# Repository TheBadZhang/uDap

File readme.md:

# uDap

uDap 是一个低成本低占面积低外围设计的单芯片 USB 设备同时提供 SWD 调试和一路虚拟串口，或者其他功能。功能可以通过上位机切换或者开启，可以实现多个功能同时工作，大幅度提升开发调试效率

> 设计要求：整个调试器物料成本小于10元，芯片主控引脚数量小于等于48，且要足够大众，产品生命周期长

核心优势如下：
1. 支持 **SWD** 调试协议，用更低的成本实现更高的性能，适配 Cortex-M 系列，STM32、GD32、AT32、CW32、PY32、HK32 等。
2. 集成 **USB2UART** 功能，支持多种波特率，满足大量数据传输和日志打印的需求
3. **UF2 bootloader**：上电长按 PB3 出现一个 U 盘，把 `firmware.uf2` 拖进去就能升级，
   不需要再接线烧录；也可以由上位机发 vendor command 直接进 bootloader
4. **功能可由上位机配置**（vendor command）：单串口+流控 / 双串口、两颗 LED 的功能、
   调试器模式切换、读芯片 UID，设置掉电保存
5. 提供 **5V/3.3V** 双路电源输出

```mermaid
flowchart LR
    PC["主机<br/>Jlink / OpenOCD / pyOCD / 串口终端"]
    subgraph DAP["uDap2 (CH32X035F8U)"]
        USBFS["USB 全速设备"]
        DAPC["CMSIS-DAP<br/>DAP.c + sw_dp.c"]
        BR["CDC 串口桥<br/>drv_uart.c"]
    end
    TGT["目标板<br/>SWCLK / SWDIO / nRESET"]
    UART["目标板 USART<br/>PB0=TX / PB1=RX"]

    PC -- "USB bulk (CMSIS-DAP)" --> USBFS
    PC -- "USB CDC ACM" --> USBFS
    USBFS --> DAPC
    USBFS --> BR
    DAPC -- "SWD 位翻转" --> TGT
    BR -- "USART" --> UART
```

### uDap-CH32X035F8U6

- 调试器 ①：**CMSIS-DAP**（bulk，WinUSB）——OpenOCD / pyOCD / probe-rs 可直接使用。**固定编入**
- 调试器 ②：**WCH-Link**（RVSWD，`1a86:8010`）——支持 CH32X03X / CH32L10X / CH32V20X /
  CH32V30X / CH58X / CH59X 六个目标族。**可选编译**（`build.ps1 -Wchlink y`，默认不编），
  编入后上电时**按住 PB3**切到另一种调试器模式
- 桥接串口 ①：CDC ACM ↔ 目标板 USART4（PB0=TX / PB1=RX），**不限制波特率**
- 桥接串口 ②（双串口模式）：CDC ACM ↔ USART2（PA2=TX2 / PA3=RX2），独立波特率
- PA2 / PA3 **双用途**：`DTR` + `RTS`（低有效）或 `TX2`/`RX2`，按键**双击**切换、掉电保存
- **串口模式决定 USB 里有几个 CDC**：单串口 + 流控只枚举 1 个 COM 口（USART2 关闭），
  双串口枚举 2 个；切换模式会重新枚举一次
- **COM1 的接收走 DMA**（USART4_RX = DMA1_Channel8，1 KB 环形缓冲）：逐字节 RXNE
  中断从每秒 10 万次降到「每半个缓冲一次」，高波特率下不再因 ISR 延迟触发 ORE
  丢字节。TX（含 COM2 全部方向）仍用中断 —— 实测给 TX 挂 DMA（Ch1 / Ch7）会让
  对应串口卡死，原因未定位。注意 USB IN 侧的总吞吐天花板（≈190~200 KiB/s）与
  DMA 无关，双口同时满速时仍受它限制
- SWD 时钟：请求 **≥6 MHz** 自动切「快路径」，**6 MHz 与更高同速**，推荐就填 6 MHz
- SWD 吞吐（STM32F411 目标，64 KiB 块）：**pyocd 262 写 / 232 读 KiB/s**、
  OpenOCD 149 / 148、probe-rs 155 / 140 —— 见「性能实测」一节
- **只留 SWD 的构建**（`--uart=n`）：USB 里没有 CDC，主机不再轮询串口端点、
  主循环也不再跑 CDC 桥接 —— 实测写 **278 KiB/s**（RAM 写，比带串口构建约 +6%）
- 串口环回：**2 Mbaud 持续满载零丢字节**（96~98 % 利用率）；分块发送时 6 Mbaud 亦字节无误
- 桥接吞吐天花板：约 **190~200 KiB/s**（≈2 Mbaud），受 USB IN 侧调度限制，与 USB 带宽无关

| 信号 | 引脚 | 说明 |
| --- | --- | --- |
| SWCLK | PA5 | SWD 时钟 |
| SWDIO | PA6 | SWD 双向数据（CFGLR 动态切输入/输出） |
| nRESET | PA7 | RST 复位 |
| DTR / TX2 | PA2 | 流控模式 = DTR（低有效）；双串口模式 = 串口2 TX |
| RTS / RX2 | PA3 | 流控模式 = RTS（低有效）；双串口模式 = 串口2 RX |
| TX | PB0 | 串口1 TX |
| RX | PB1 | 串口1 RX |
| 模式按键 | PB3 | 上拉输入，按下接地；上电一直按住 >1.2 s 进 UF2，运行中双击切模式（单模式=串口/双模式=调试器） |
| DAP 灯 | PB11 | 低电平点亮；默认 = CMSIS-DAP 连接时亮（也可由 vendor command 切换用途） |
| UART 灯 | PB12 | 低电平点亮；默认 = 亮表示双串口模式（也可由 vendor command 切换用途） |
| USB | PC16 = DPDM / PC17 = DP | 固定复用 |

### uDap-CH32X033

与 uDap-CH32X035F8U6 **同一份固件**（CH32X033 的 SDK/外设与 X035 相同，差别只有引脚
与 USB PD/CC 外设），换一张板级表就行：

```powershell
.\build.ps1 -Board ch32x033
```

| 信号 | 引脚 | 说明 |
| --- | --- | --- |
| SWCLK / SWDIO | PA1 / PA0 | CMSIS-DAP + WCH-Link（互斥），默认方案 `pa0_pa1` |
| nRESET | PA9 | 目标复位，低有效（开漏模拟） |
| RX1 / TX1 | PA3 / PA2 | 串口1，USART2 默认引脚 |
| TX2 / RX2 | PA10 / PA11 | 串口2，USART1 + `USART1_RM = 01` |
| 模式按键 | PC3 | 上拉输入，按下接地；长按进 UF2，双击切模式 |
| LED（DAP / UART） | PB7 / PB1 | 低电平点亮 |
| USB | PC16 = DPDM / PC17 = DP | 固定复用 |
| DTR / RTS | 无 | 本板没有这两个脚，默认串口模式为双串口 |

### uDap-CH32V203F8U6

### uDap-CH572

### uDap-CH552G

## 对照测试

本节把「本板 uDAP 以外的第三方 CMSIS-DAP 探针」的 SWD 吞吐测试集中在一处：
测试方法、五块探针的标识、以及**唯一的总表**（按频率 × 块大小 × 调试器排成矩阵）。
各探针不再单独列表，避免与总表重复。

#### 测试对象与接线

| 项目 | 值 |
| --- | --- |
| 目标 | STM32F411CEU6（CPUID `0x410FC241`、DBGMCU IDCODE `0x10006431` → DEV_ID `0x431`、512 KB Flash、128 KB SRAM） |
| 测试区 | 目标 SRAM `0x20000000` 起（与 18.1、18.5 同一地址，便于对比） |
| 接线 | 探针 SWCLK / SWDIO / GND 接目标，目标单独供电 |

#### 测量流程

1. 打开探针会话、`halt` 目标；
2. **整块备份**测试区，测完**逐字写回**并 `resume`，不破坏目标正在跑的程序；
3. 填充模式 `0xA5A50000 | i`（变化的 pattern，能暴露地址线/数据线问题与突发顺序错误）；
4. 每个「频率 × 块大小」组合先预热一次，再正式测 5 次；写、读**各自单独计时**，
   读回**逐字校验**；失败（ACK 错 / 超时 / 数据不符）记 `ok=0` 并继续；
5. 每组取**中位数**（不取平均，避免个别离群值污染）。

> 本板 uDAP 的 OpenOCD 数据于 2026-10-28 使用 `firmware/tools/speed.ps1 -Rounds 1` 逐组合复测；每组预热 2 轮后正式测 1 轮，因此该探针的数据为单次结果，不适用上述 5 次中位数流程。

#### 参数与工具

| 参数 | 取值 |
| --- | --- |
| 频率 | **1 / 3 / 6 / 9 / 12 / 15 MHz**（6 档；表头「1、3、6…」即 MHz） |
| 块大小 | **1 / 4 / 16 / 64 KiB**（4 档） |
| 重复次数 | 每组合 **5 次**，取中位数 |
| 工具 | **pyocd 0.45.1** 与 **OpenOCD 0.12.0**，同一块探针各扫一遍 |

两个工具都支持在**同一条会话里改频率**（pyocd 用 `probe.set_clock()`，OpenOCD 用
`adapter speed`），所以整轮扫描只连接一次，不会把反复连接的固定开销算进结果。

> 表里的频率是**请求值**，不是实测 SWCLK。探针可能把请求值映射成离散分频，
> 实际时钟与请求值有差距（见下面「注意事项」里的低端反常）。

#### 五块探针的标识

| 探针 | 主机侧名称 | 序列号 | CMSIS-DAP | 备注 |
| --- | --- | --- | --- | --- |
| **本板 uDAP** | `uDAP CMSIS-DAP` | `923CABCDFB83BD7AFFFFFFFF` | 0.1.0 | 本仓库固件；快路径时钟约 6 MHz；无 WebUSB/MSC |
| **FanX Tek DAPLink** | `Arm DAPLink CMSIS-DAP` | `38b30f94aae9ddfa01` | FW 2.1.0，v2(bulk) | SWD+JTAG+SWO-UART；`Packet Count = 4` |
| **CherryUSB CH32V305** | `CherryUSB CMSIS-DAP` | `39D9ABCD` | FW 2.1.1，v2 | 自制板；**pyocd 不可用**（见下） |
| **LuatOS Air32 MINI** | `ABrobot CMSIS-DAP` | `000100011a5a5bb6000000000003f60fa5a5a5a597969908` | FW 2.1.0，v1(HID)+v2 | `Packet Count = 100`；**读快于写**；**吞吐会跳档**（见下） |
| **SLogic 8** | `SIPEED RV CMSIS-DAP` | `012345ABCDEF` | FW 2.1.0，v2 | Sipeed 板，VID:PID 为 `d6e7:3507`（**与其余四块不同**）；`Packet Count = 8` |

> 前四块的 VID:PID 都是 `0d28:0204`，同时插入时**必须**用序列号区分：
> OpenOCD 侧 `-c "adapter serial <id>"`，pyocd 侧 `unique_id`。序列号用 `pyocd list` 查。

#### 总表：OpenOCD（写 / 读，KiB/s；本板 uDAP 为单次结果，其余为 5 次中位数）

| 调试器 | 块大小 | 1 | 3 | 6 | 9 | 12 | 15 |
| --- | --- | ---: | ---: | ---: | ---: | ---: | ---: |
| 本板 uDAP (CH32X035) | 1 KiB | 26 / 24 | 60 / 61 | 259 / 219 | 234 / 232 | 247 / 233 | 255 / 218 |
| 本板 uDAP (CH32X035) | 4 KiB | 27 / 25 | 60 / 64 | 268 / 248 | 269 / 249 | 267 / 246 | 269 / 248 |
| 本板 uDAP (CH32X035) | 16 KiB | 27 / 25 | 61 / 64 | 267 / 249 | 267 / 249 | 268 / 249 | 267 / 250 |
| 本板 uDAP (CH32X035) | 64 KiB | 27 / 25 | 61 / 64 | 266 / 251 | 266 / 250 | 267 / 251 | 267 / 251 |
| FanX Tek DAPLink | 1 KiB | 177 / 179 | 250 / 237 | 278 / 279 | 314 / 307 | 500 / 333 | 500 / 366 |
| FanX Tek DAPLink | 4 KiB | 185 / 197 | 258 / 269 | 318 / 323 | 302 / 313 | 462 / 437 | 456 / 444 |
| FanX Tek DAPLink | 16 KiB | 185 / 193 | 258 / 262 | 315 / 325 | 303 / 304 | 461 / 458 | 464 / 470 |
| FanX Tek DAPLink | 64 KiB | 182 / 183 | 258 / 263 | 307 / 307 | 302 / 303 | 457 / 469 | 458 / 468 |
| CherryUSB CH32V305 | 1 KiB | 107 / 125 | 200 / 200 | 242 / 250 | 333 / 333 | 390 / 390 | 475 / 378 |
| CherryUSB CH32V305 | 4 KiB | 116 / 119 | 195 / 205 | 254 / 269 | 412 / 399 | 426 / 400 | 425 / 400 |
| CherryUSB CH32V305 | 16 KiB | 117 / 120 | 197 / 206 | 261 / 275 | 427 / 398 | 428 / 405 | 450 / 410 |
| CherryUSB CH32V305 | 64 KiB | 117 / 121 | 198 / 206 | 261 / 275 | 426 / 396 | 425 / 400 | 439 / 416 |
| LuatOS Air32 MINI | 1 KiB | 130 / 125 | 200 / 200 | 248 / 250 | 277 / 250 | 250 / 234 | 250 / 250 |
| LuatOS Air32 MINI | 4 KiB | 128 / 128 | 216 / 208 | 241 / 235 | 267 / 267 | 261 / 268 | 267 / 267 |
| LuatOS Air32 MINI | 16 KiB | 130 / 128 | 213 / 207 | 251 / 246 | 276 / 275 | 268 / 265 | 274 / 267 |
| LuatOS Air32 MINI | 64 KiB | 129 / 130 | 215 / 210 | 252 / 245 | 276 / 274 | 268 / 265 | 272 / 269 |
| SLogic 8 (Sipeed) | 1 KiB | 59 / 58 | 105 / 105 | 130 / 129 | 147 / 143 | 169 / 155 | 148 / 151 |
| SLogic 8 (Sipeed) | 4 KiB | 60 / 60 | 108 / 108 | 132 / 131 | 157 / 147 | 166 / 159 | 166 / 160 |
| SLogic 8 (Sipeed) | 16 KiB | 59 / 59 | 110 / 109 | 135 / 131 | 155 / 148 | 166 / 158 | 166 / 159 |
| SLogic 8 (Sipeed) | 64 KiB | 59 / 59 | 110 / 109 | 135 / 131 | 154 / 148 | 167 / 159 | 166 / 159 |

> 本板 uDAP 的 pyOCD 数据于 2026-10-28 使用 `firmware/tools/pyocd_speed.py` 逐组合复测；每组预热 1 轮后正式测 1 轮，因此该探针的数据为单次结果，不适用下表其余探针的 5 次中位数统计。

#### 总表：pyocd（写 / 读，KiB/s；本板 uDAP 为单次结果，其余为 5 次中位数）

| 调试器 | 块大小 | 1 | 3 | 6 | 9 | 12 | 15 |
| --- | --- | ---: | ---: | ---: | ---: | ---: | ---: |
| 本板 uDAP (CH32X035) | 1 KiB | 47 / 17 | 107 / 43 | 334 / 189 | 342 / 186 | 326 / 188 | 302 / 198 |
| 本板 uDAP (CH32X035) | 4 KiB | 30 / 22 | 68 / 57 | 280 / 227 | 281 / 224 | 278 / 227 | 276 / 229 |
| 本板 uDAP (CH32X035) | 16 KiB | 27 / 23 | 63 / 61 | 268 / 234 | 267 / 234 | 267 / 235 | 268 / 234 |
| 本板 uDAP (CH32X035) | 64 KiB | 27 / 24 | 62 / 63 | 263 / 237 | 264 / 237 | 264 / 238 | 263 / 237 |
| FanX Tek DAPLink | 1 KiB | 229 / 234 | 333 / 338 | 413 / 400 | 403 / 410 | 678 / 670 | 655 / 677 |
| FanX Tek DAPLink | 4 KiB | 247 / 245 | 375 / 370 | 457 / 448 | 461 / 456 | 835 / 769 | 837 / 774 |
| FanX Tek DAPLink | 16 KiB | 251 / 246 | 389 / 372 | 475 / 452 | 475 / 450 | 881 / 777 | 882 / 779 |
| FanX Tek DAPLink | 64 KiB | 252 / 244 | 391 / 373 | 479 / 451 | 479 / 452 | 893 / 778 | 894 / 781 |
| CherryUSB CH32V305 | 1 KiB | — | — | — | — | — | — |
| CherryUSB CH32V305 | 4 KiB | — | — | — | — | — | — |
| CherryUSB CH32V305 | 16 KiB | — | — | — | — | — | — |
| CherryUSB CH32V305 | 64 KiB | — | — | — | — | — | — |
| LuatOS Air32 MINI | 1 KiB | 166 / 157 | 264 / 283 | 259 / 336 | 273 / 321 | 270 / 326 | 270 / 323 |
| LuatOS Air32 MINI | 4 KiB | 176 / 164 | 287 / 314 | 287 / 362 | 293 / 364 | 296 / 362 | 291 / 352 |
| LuatOS Air32 MINI | 16 KiB | 179 / 163 | 295 / 313 | 296 / 358 | 298 / 362 | 298 / 357 | 298 / 365 |
| LuatOS Air32 MINI | 64 KiB | 179 / 162 | 296 / 313 | 296 / 359 | 297 / 362 | 298 / 359 | 296 / 359 |
| SLogic 8 (Sipeed) | 1 KiB | 66 / 65 | 129 / 126 | 163 / 154 | 190 / 180 | 207 / 194 | 207 / 194 |
| SLogic 8 (Sipeed) | 4 KiB | 68 / 66 | 137 / 131 | 176 / 163 | 207 / 190 | 226 / 207 | 226 / 208 |
| SLogic 8 (Sipeed) | 16 KiB | 69 / 66 | 139 / 131 | 178 / 163 | 210 / 190 | 230 / 208 | 231 / 208 |
| SLogic 8 (Sipeed) | 64 KiB | 69 / 66 | 139 / 131 | 179 / 163 | 211 / 190 | 232 / 208 | 232 / 208 |

> CherryUSB CH32V305 的 pyocd 一栏全为「—」：这块自制探针在 pyocd 下不可用，
> 而且会把探针卡死到需要拔插 USB 才能恢复，见下面「注意事项」。
>
> 「只留 SWD」构建（`--uart=n`，USB 里没有 CDC）在同一台机器/同一目标上实测写
> **278 KiB/s**；上表带串口构建的写约 263~265 KiB/s，即去掉串口开销带来约 6% 的
> 提升 —— 收益来自主机不再轮询 CDC 端点、主循环也不再每条 DAP 命令后跑一次 CDC 桥接。

#### 从总表读出的结论

1. **形状分三类。**
   - **本板 uDAP 是「三级」**：1~3 MHz 走慢路径（64 KiB 写 24→51），**6 MHz 跳约 3 倍**，
     之后 6~15 MHz 完全平坦（151~154）—— 就是 18.1 说的快/慢路径阈值（6 MHz），
     且快路径的实际 SWCLK 由指令数钉死（约 6 MHz），请求再高也不变。
   - **FanX Tek / CH32V305 / Air32 是「台阶式」**：请求频率被映射成离散分频，所以
     吞吐随频率分段跳、跳到台阶之上就持平。FanX 的台阶在 9~12 MHz 之间（OpenOCD
     64 KiB 写 302→457），CH32V305 与 Air32 在 6~9 MHz 之间（OpenOCD 分别 261→426、
     252→276）。**对这类探针，跳到台阶之上再往上填没有收益。**
   - **SLogic 8 是「单调缓升 + 饱和」**：从 59 一路升到 12 MHz 的 167（OpenOCD），
     没有明显台阶，12 MHz 之后持平。低频段它比 uDAP 快得多（1 MHz 59 vs 24）。
2. **本板 uDAP 在五者里最慢，差距集中在两头**：低频段 1 MHz（64 KiB 写）uDAP 24，
   其它 59~182；高频段 6 MHz 及以上 uDAP 151，其它 135~458。低频差是因为慢路径的
   半周期延时太大，高频差是因为快路径被约 6 MHz 的实际时钟钉住。
3. **块大小基本不影响吞吐**：五块探针、两个工具、全频段下 1/4/16/64 KiB 的差异几乎都在
   10% 以内（uDAP 与 SLogic 8 最平，<3%）。**唯一明显的是 pyocd 的小块写**：uDAP 在
   6 MHz 时 1 KiB 写 383 比 64 KiB 写 261 高 **47%**，FanX 与 SLogic 8 也是同方向
   （小块更快）—— 这是主机侧把多个写命令流水化的效果；反过来**小块读更慢**（要等回包）。
   注意这一列对 uDAP 可能偏高，见下面「注意事项」第 1 条。
4. **pyocd 全面高于 OpenOCD**，比值因探针而异：约 1.7~2.0×（同为 64 KiB、6~12 MHz）。
   原因是 OpenOCD 把在飞命令数夹在写死的 `MAX_PENDING_REQUESTS = 3`（`cmsis_dap.c`），
   而 pyocd 不设这个上限。Air32 的 `DAP_PACKET_COUNT = 100` 也改变不了这一点 ——
   限制在主机侧，不在探针侧。
5. **读写关系**：uDAP、FanX、CH32V305、SLogic 8 都是**读 ≤ 写或基本对称**，
   **只有 Air32 是读明显快于写**（pyocd 64 KiB @12 MHz：写 298 / 读 359）。
   要读大块数据时 Air32 在低频段是五者里最快的。

#### 复现命令

```powershell
# 扫一块探针（两个工具都扫；默认 1/3/6/9/12/15 MHz × 1/4/16/64 KiB × 5 次）
python firmware/tools/probe_swd_sweep.py --label "FanX Tek DAPLink" ^
    --probe 38b30f94aae9ddfa01 --tool both --reps 5 ^
    --csv firmware/build/sweep_fanx_tek.csv

# 只跑一个工具 / 自定义频率与块大小
python firmware/tools/probe_swd_sweep.py --tool openocd --freqs 1000,9000,15000 --sizes 1024,65536
```

逐次原始结果写入 `--csv`（默认落在 `firmware/build/`，该目录不入库）。
§18 其余小节各自的复现命令见那一节本身（18.1 / 18.2 / 18.4 / 18.5）。

#### 附：pyocd 的 "at X kB/s" 不可信

pyocd 的烧录日志：

```
Erased 65536 bytes (4 sectors), programmed 51200 bytes (50 pages), identical 0 bytes (0 pages) at 23.67 kB/s
```

该速度 = `program_byte_count / (erase_time + program_time)`（见 `pyocd/flash/loader.py` 的
`_log_performance`）。当写入数据与 Flash 现有一致时，smart_flash 会跳过擦除与编程，
**分母塌掉、分子照旧**，数字虚高数倍。

判据：**出现 `Erased 0 bytes (0 sectors)` 即为跳过烧录，该速度无意义。**

| 50 KiB @12 MHz | 编程耗时 | 速度 |
| --- | --- | --- |
| 真实烧录 | 743 ms | 68.9 KiB/s |
| 跳过烧录 | — | 160.67 kB/s（虚高，实为读回带宽） |

强制真实烧录：加 `-O smart_flash=False`，或每次换一份随机数据。

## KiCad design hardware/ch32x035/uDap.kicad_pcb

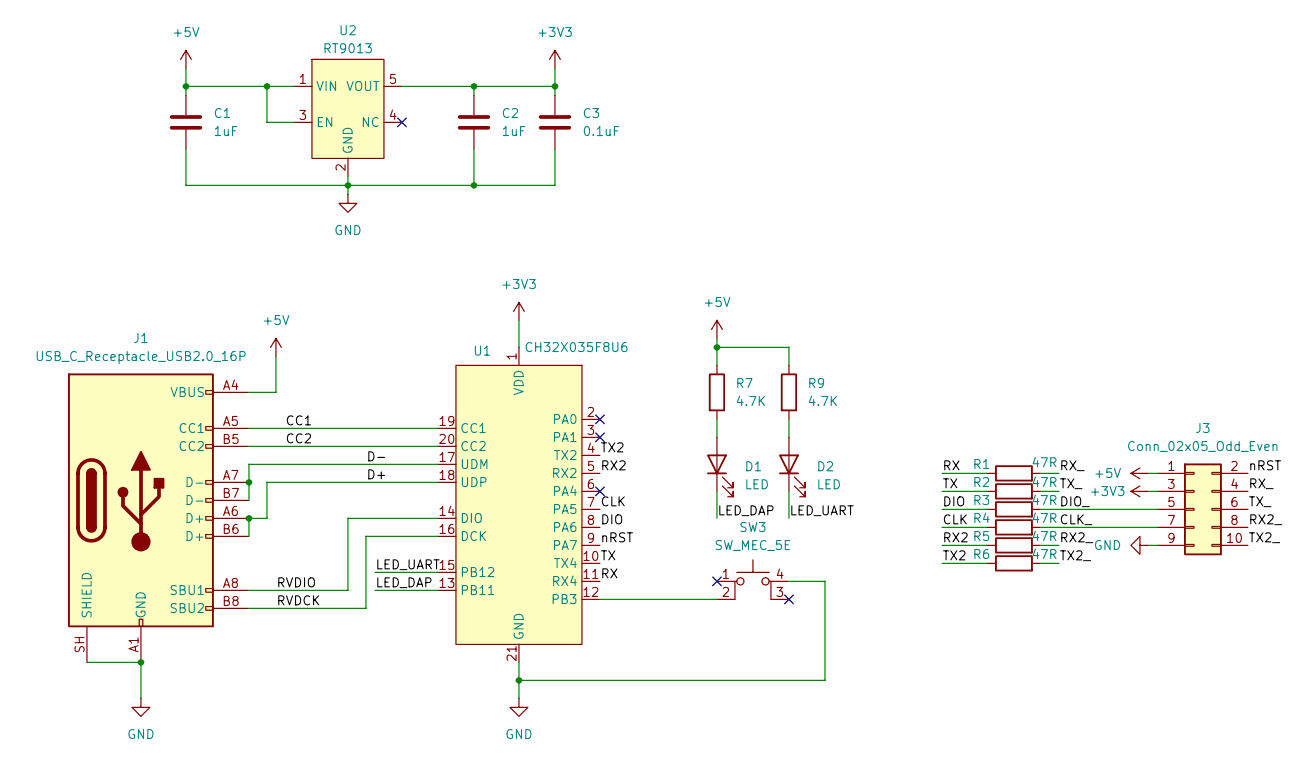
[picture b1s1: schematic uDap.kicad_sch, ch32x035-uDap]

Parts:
C1, C2: 1uF; C_0603_1608Metric
C3: 0.1uF; C_0603_1608Metric
D1, D2: LED; LED_0603_1608Metric
J1: USB_C_Receptacle_USB2.0_16P; USB_C_Receptacle_GCT_USB4105-xx-A_16P_TopMnt_Horizontal
J3: Conn_02x05_Odd_Even; 双面贴片排针2x5
R1, R2, R3, R4, R5, R6: 47R; R_0603_1608Metric
R7, R9: 4.7K; R_0603_1608Metric
SW3: SW_MEC_5E; KEY-SMD_4P-L4.2-W3.4-P2.15-LS4.5-TL_1
U1: CH32X035F8U6; QFN-20-1EP_3x3mm_P0.4mm_EP1.65x1.65mm
U2: RT9013; SOT-23-5

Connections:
+3V3: C2.1, C3.1, J3.3, U1.1 (VDD), U2.5 (VOUT)
+5V: C1.1, J1.A4 (VBUS), J1.A9 (VBUS), J1.B4 (VBUS), J1.B9 (VBUS), J3.1, R7.1, R9.1, U2.1 (VIN), U2.3 (EN)
/CC1: J1.A5 (CC1), U1.19 (CC1)
/CC2: J1.B5 (CC2), U1.20 (CC2)
/CLK: R4.1, U1.7 (PA5)
/CLK_: J3.7, R4.2
/D+: J1.A6 (D+), J1.B6 (D+), U1.18 (UDP)
/D-: J1.A7 (D-), J1.B7 (D-), U1.17 (UDM)
/DIO: R3.1, U1.8 (PA6)
/DIO_: J3.5, R3.2
/LED_DAP: D1.1 (K), U1.13 (PB11)
/LED_UART: D2.1 (K), U1.15 (PB12)
/RVDCK: J1.B8 (SBU2), U1.16 (DCK)
/RVDIO: J1.A8 (SBU1), U1.14 (DIO)
/RX: R1.1, U1.11 (RX4)
/RX2: R5.1, U1.5 (RX2)
/RX2_: J3.8, R5.2
/RX_: J3.4, R1.2
/TX: R2.1, U1.10 (TX4)
/TX2: R6.1, U1.4 (TX2)
/TX2_: J3.10, R6.2
/TX_: J3.6, R2.2
/nRST: J3.2, U1.9 (PA7)
GND: C1.2, C2.2, C3.2, J1.A1 (GND), J1.A12 (GND), J1.B1 (GND), J1.B12 (GND), J1.SH (SHIELD), J3.9, SW3.4 (A), U1.21 (GND), U2.2 (GND)
unnamed: D1.2 (A), R7.2
unnamed: D2.2 (A), R9.2
unnamed: SW3.2, U1.12 (PB3)

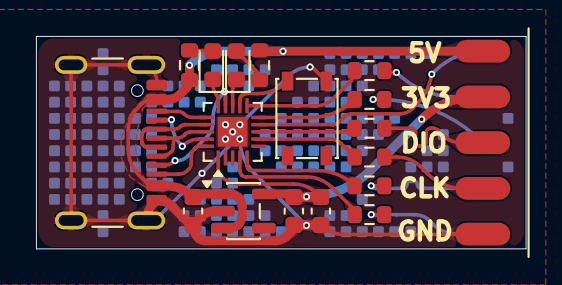
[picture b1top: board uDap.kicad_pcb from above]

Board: 2 copper layers, 27.2 x 11.8 mm, 18 parts (0 on the bottom side), 27 nets.

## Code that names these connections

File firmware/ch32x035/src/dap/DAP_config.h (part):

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// 走这里的函数表，换驱动只改绑定，不用改本文件。
#include "swd_gpio.h"

// 板级引脚（状态灯 PB11/PB12 等）
#include "board_pin_map.h"

#ifndef __STATIC_INLINE
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    return 0U;
}

// SWCLK = PA5，SWDIO = PA6（引脚号见 src/swd_pin_map.h 的 SWD_PIN_VARIANT）
//
// ⚠️ 这一层是**每比特**调用的边沿级原语，必须是编译期展开的 inline：
// 快路径的一个 SWCLK 周期就等于两条 store 之间的指令数，中间插一次间接调用
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__STATIC_FORCEINLINE void PIN_nTRST_OUT(uint32_t bit) { (void)bit; }

// nRESET（目标复位，低有效）是否启用由 src/swd_pin_map.h 决定：
// 本板目标 nRESET 接到 PA7，默认启用；SWD_NRESET_ENABLE = 0 时，
// 三个操作退化为空操作。SWDIO 必须使用 PA6，避免与 PA7 复位脚冲突。
#if SWD_NRESET_ENABLE

// nRESET 在 CFGLR 中占第 SWD_NRESET_CFGLR_SHIFT 起的 4 位（每脚 4 位）
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// 状态指示灯
//
// 本板有两颗灯，都是**低电平点亮**（引脚见 src/board_pin_map.h）：
//   PB11 = DAP 指示灯：CMSIS-DAP 的 Connect LED，主机（调试器软件）连接到 DAP
//          时点亮，由本文件的 LED_CONNECTED_OUT() 驱动。
//   PB12 = UART 指示灯：亮 = 双串口模式，灭 = 串口1 + DTR/RTS 模式，
//          由 src/drv/drv_uart.c 的模式小节驱动（不在这里，避免两处抢同一个引脚）。
//
// 由 DAP.c 的 DAP_HostStatus(ID_DAP_HostStatus=0x01) 驱动：
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}

__STATIC_INLINE void DAP_SETUP(void) {
    // GPIOB 给状态灯（PB12）用，GPIOA 给 SWD 用（SWCLK = PA5 / SWDIO = PA6）
    RCC_APB2PeriphClockCmd(SWD_PORT_CLOCK | RCC_APB2Periph_GPIOB, ENABLE);

    // 先把输出数据寄存器置为「灭」，再切成推挽输出，避免初始化瞬间闪一下。
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// 返回 1 表示已实现 —— 主机（OpenOCD / pyocd）执行 reset 时会优先走这里，
// 而不是只靠 SWJ_Pins 逐次拉线。
//
// 默认通过 PA7 拉低 nRESET 20 ms 后释放；关闭 SWD_NRESET_ENABLE 时返回 0，
// 主机退回 SWD SYSRESETREQ。
__STATIC_INLINE uint8_t RESET_TARGET(void) {
#if SWD_NRESET_ENABLE
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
